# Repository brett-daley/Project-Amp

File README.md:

# Project-Amp
Small, portable headphone amplifier for the guitar. Complete with EQ and distortion.

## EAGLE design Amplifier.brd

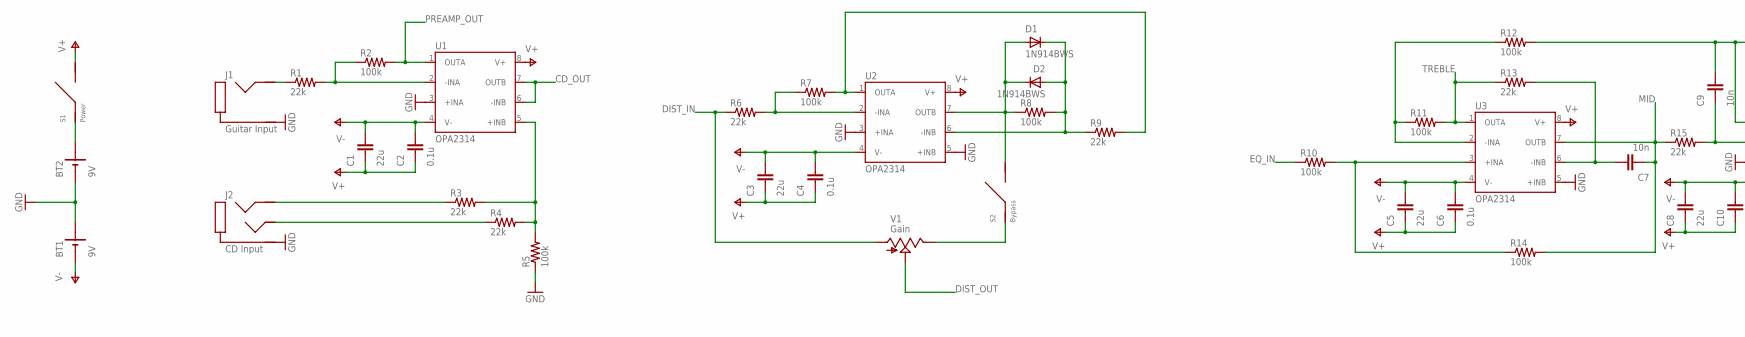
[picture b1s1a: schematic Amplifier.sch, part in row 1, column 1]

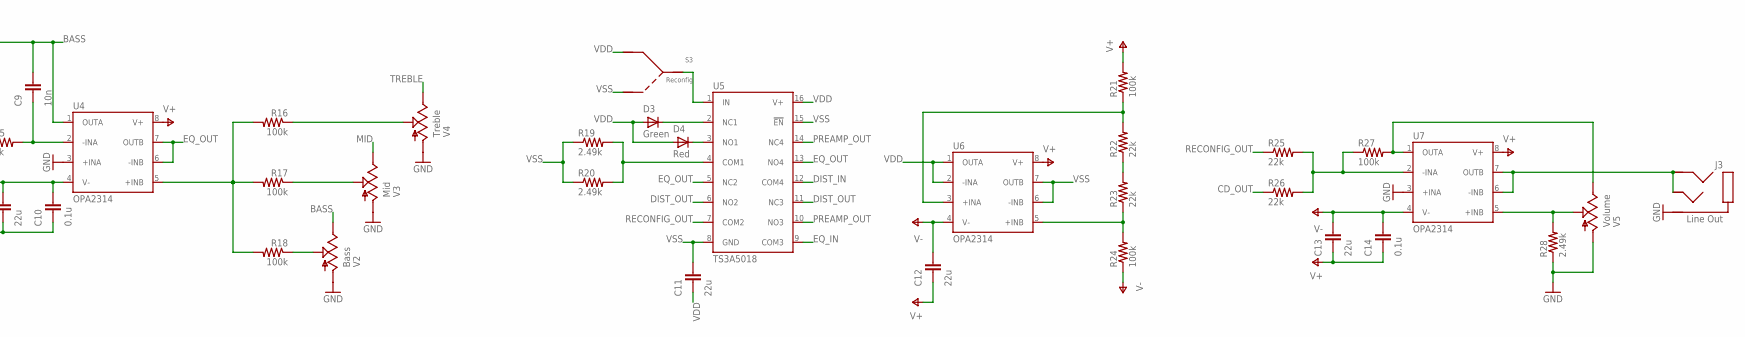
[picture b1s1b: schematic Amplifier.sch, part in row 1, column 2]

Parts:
BT1, BT2: 9V; 9V59X
C1, C3, C5, C8, C11, C12, C13: 22u; C1206
C2, C4, C6, C10, C14: 0.1u; C0402
C7, C9: 10n; ECW-F6103HL
D1, D2: 1N914BWS; SOD-323F
D3: Green; R0402
D4: Red; R0402
J1: Guitar Input; RA49C12B
J2: CD Input; SJ1-3513-SMT-TR
J3: Line Out; SJ1-3513-SMT-TR
R1, R3, R4, R6, R9, R13, R15, R22, R23, R25, R26: 22k; R0402
R2, R5, R7, R8, R10, R11, R12, R14, R16, R17, R18, R21, R24, R27: 100k; R0402
R19, R20, R28: 2.49k; R0402
S1: Power; TMS6T5B2M2RE
S2: Bypass; TMS6T5B2M2RE
S3: Reconfig; TMS1T5B2M2R
U1, U2, U3, U4, U6, U7: OPA2314; 8-SOIC
U5: TS3A5018; 16-SOIC
V1: Gain; P0915N-EC15BR10K
V2: Bass; P0915N-EC15BR10K
V3: Mid; P0915N-EC15BR10K
V4: Treble; P0915N-EC15BR10K
V5: Volume; P0915N-EC15BR10K

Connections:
BASS: C9.1, R12.2, U4.1 (OUTA), V2.3 (E)
CD_OUT: R26.1, U1.6 (-INB), U1.7 (OUTB)
DIST_IN: R6.1, U5.12 (COM4), V1.1 (A)
DIST_OUT: U5.6 (NO2), U5.11 (NC3), V1.2 (S)
EQ_IN: R10.1, U5.9 (COM3)
EQ_OUT: U4.6 (-INB), U4.7 (OUTB), U5.5 (NC2), U5.13 (NO4)
GND: BT1.4 (+), BT1.5 (+), BT1.6 (+), BT2.1 (-), BT2.2 (-), BT2.3 (-), J1.S1 (COM), J1.S2 (COM), J2.1 (COM), J3.1 (COM), R5.1, R28.1, U1.3 (+INA), U2.3 (+INA), U2.5 (+INB), U3.5 (+INB), U4.3 (+INA), U7.3 (+INA), V2.1 (A), V3.1 (A), V4.1 (A), V5.1 (A)
LINE_OUT: J3.2 (LEFT), J3.3 (RIGHT), U7.6 (-INB), U7.7 (OUTB)
MID: C7.2, R14.2, R15.1, U3.7 (OUTB), V3.3 (E)
unnamed: R21.1, R22.2, U6.3 (+INA)
unnamed: J1.T (SIG), R1.1
unnamed: R1.2, R2.1, U1.2 (-INA)
unnamed: R3.2, R4.2, R5.2, U1.5 (+INB)
unnamed: R22.1, R23.2
unnamed: J2.2 (LEFT), R4.1
unnamed: J2.3 (RIGHT), R3.1
unnamed: R23.1, R24.2, U6.5 (+INB)
unnamed: D3.2 (C), U5.2 (NC1)
unnamed: R19.2, R20.2, U5.4 (COM1)
unnamed: D1.2 (A), D2.1 (C), R8.1, S2.1, U2.7 (OUTB)
unnamed: D1.1 (C), D2.2 (A), R8.2, R9.1, U2.6 (-INB)
unnamed: R7.2, R9.2, U2.1 (OUTA)
unnamed: R6.2, R7.1, U2.2 (-INA)
unnamed: S2.3, V1.3 (E)
unnamed: R16.2, R17.2, R18.2, U4.5 (+INB)
unnamed: R16.1, V4.2 (S)
unnamed: R17.1, V3.2 (S)
unnamed: R18.1, V2.2 (S)
unnamed: R10.2, R14.1, U3.3 (+INA)
unnamed: R11.1, R12.1, U3.2 (-INA)
unnamed: C7.1, R13.2, U3.6 (-INB)
unnamed: C9.2, R15.2, U4.2 (-INA)
unnamed: R27.2, U7.1 (OUTA), V5.3 (E)
unnamed: R25.2, R26.2, R27.1, U7.2 (-INA)
unnamed: R28.2, U7.5 (+INB), V5.2 (S)
unnamed: BT2.4 (+), BT2.5 (+), BT2.6 (+), S1.3
unnamed: S3.2 (COM), U5.1 (IN)
unnamed: D4.2 (C), U5.3 (NO1)
PREAMP_OUT: R2.2, U1.1 (OUTA), U5.10 (NO3), U5.14 (NC4)
RECONFIG_OUT: R25.1, U5.7 (COM2)
TREBLE: R11.2, R13.1, U3.1 (OUTA), V4.3 (E)
V+: C1.2, C2.2, C3.2, C4.2, C5.2, C6.2, C8.2, C10.2, C12.2, C13.2, C14.2, R21.2, S1.1, U1.8 (V+), U2.8 (V+), U3.8 (V+), U4.8 (V+), U6.8 (V+), U7.8 (V+)
V-: BT1.1 (-), BT1.2 (-), BT1.3 (-), C1.1, C2.1, C3.1, C4.1, C5.1, C6.1, C8.1, C10.1, C12.1, C13.1, C14.1, R24.1, U1.4 (V-), U2.4 (V-), U3.4 (V-), U4.4 (V-), U6.4 (V-), U7.4 (V-)
VDD: C11.2, D3.1 (A), D4.1 (A), S3.3 (POS1), U5.16 (V+), U6.1 (OUTA), U6.2 (-INA)
VSS: C11.1, R19.1, R20.1, S3.1 (POS2), U5.8 (GND), U5.15 (!EN), U6.6 (-INB), U6.7 (OUTB)

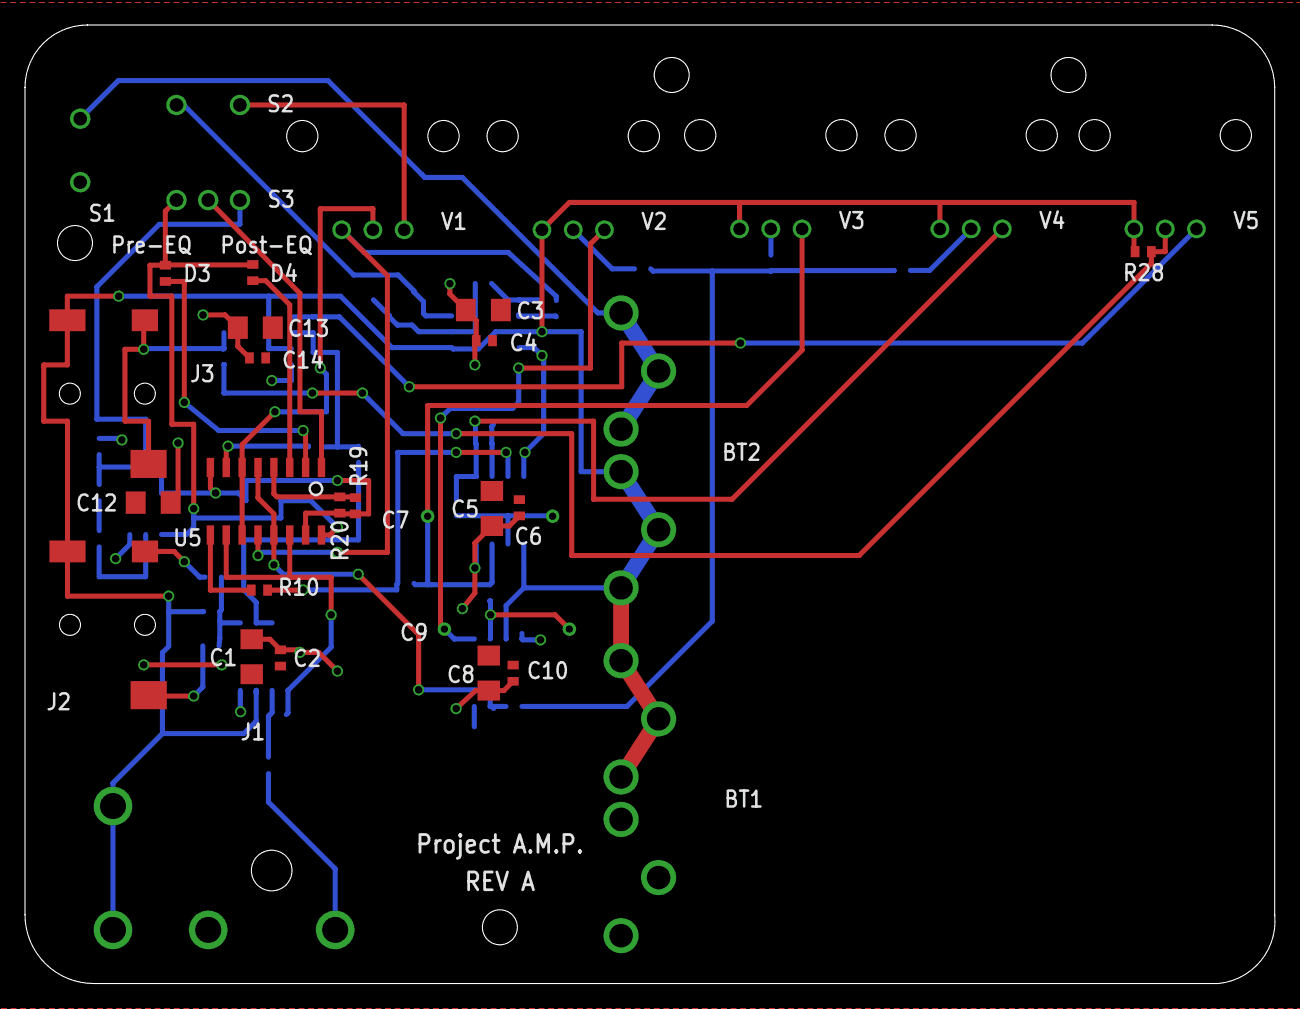
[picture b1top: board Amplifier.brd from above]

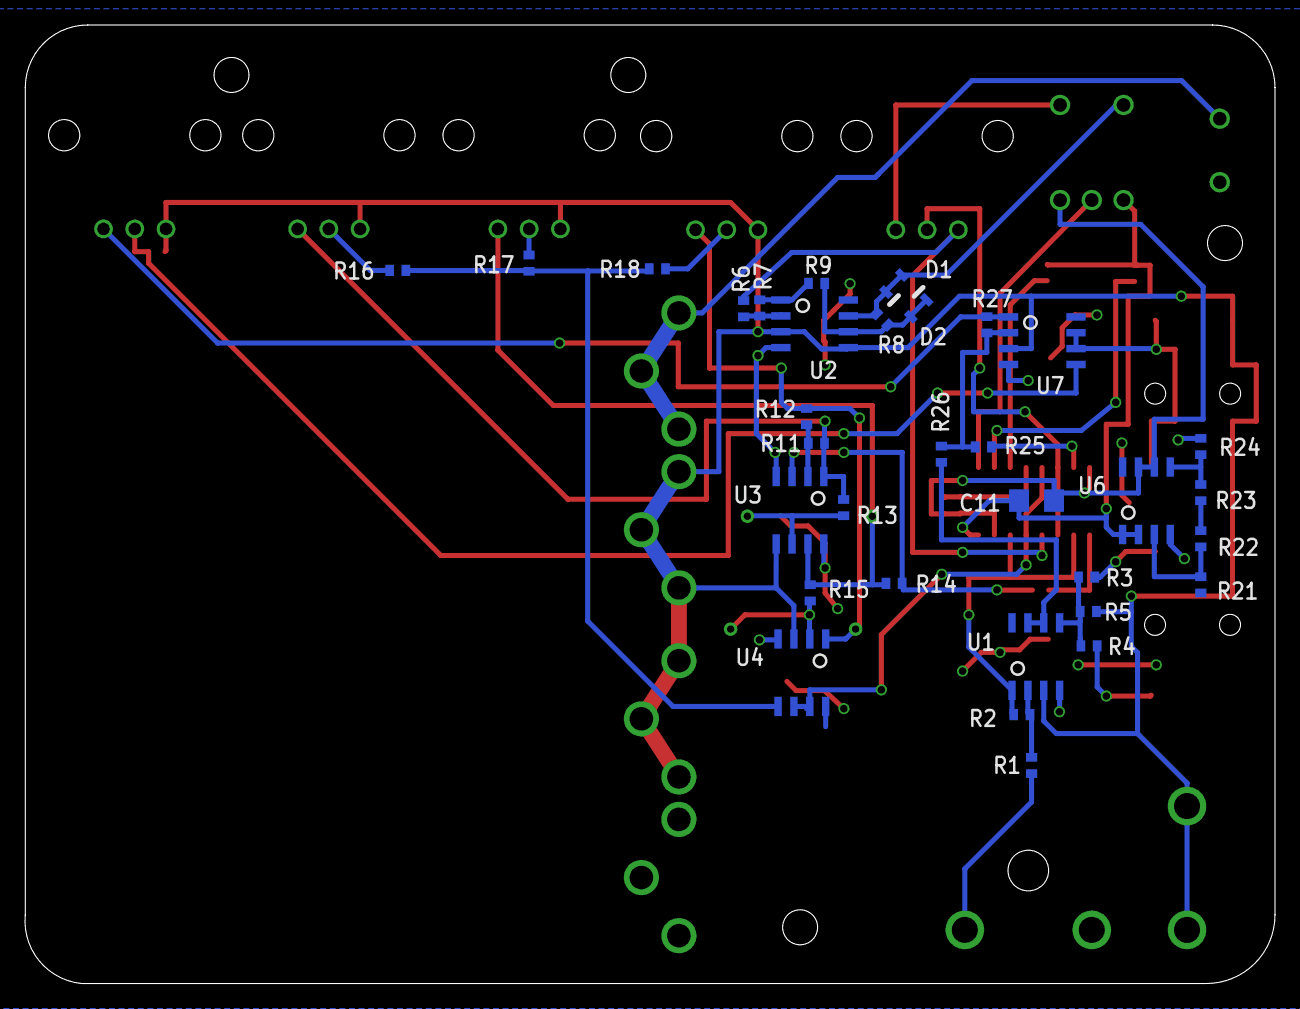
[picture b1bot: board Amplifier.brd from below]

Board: 2 copper layers, 100.0 x 76.7 mm, 66 parts (33 on the bottom side), 45 nets.

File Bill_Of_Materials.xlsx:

Item | Reference | Description | Manufacturer | Manufacturer PN | Digi-Key PN | Quantity
1 | BT1,BT2 | CONN BATT MALE/FEM 9V HORZ SNAP-ON | Keystone Electronics | 593/594 | 36-593-ND/36-594-ND | 2
2 | C1,C3,C5,C8,C11,C12,C13 | 22µF 25V Ceramic Capacitor X5R 1206 (3216 Metric) 0.126" L x 0.063" W (3.20mm x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 | Murata Electronics North America | GRM31CR61E226KE15L | 490-5527-2-ND | 7
3 | C2,C4,C6,C10,C14 | 0.10µF 25V Ceramic Capacitor X5R 0402 (1005 Metric) 0.039" L x 0.020" W (1.00mm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 | Murata Electronics North America | GRM155R61E104KA87D | 490-5920-1-ND | 5
4 | C7,C9 | 10000pF Film Capacitor 630V Polypropylene (PP), Metallized Radial 0.492" L x 0.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 | Panasonic Electronic Components | ECW-F6103HL | P12109-ND | 2
5 | D1,D2 | DIODE GEN PURP 75V 150MA SOD323F | Fairchild Semiconductor | 1N914BWS | 1N914BWSCT-ND | 2
6 | D3 | Green 569nm LED Indication Discrete 1.9V Clear Lens 0402 (1005 Metric) | Rohm Semiconductor | SML-P11MTT86 | 511-1652-1-ND | 1
7 | D4 | Red 621nm LED Indication Discrete 1.8V Clear Lens 0402 (1005 Metric) | Rohm Semiconductor | SML-P11UTT86 | 511-1653-1-ND | 1
8 | J1 | 6.35mm (0.250", 1/4") - Headphone Phone Jack Stereo Connector Solder | Switchcraft Inc. | RA49C12B | SC2083-ND | 1
9 | J2,J3 | 3.50mm (0.141", 1/8", Mini Plug) - Headphone Phone Jack Stereo Connector Solder | CUI Inc. | SJ1-3513-SMT-TR | CP1-3513SJCT-ND | 2
10 | R1,R3,R4,R6,R9,R13,R15,R22,R23,R25,R26 | RES SMD 22K OHM 1% 1/16W 0402 | Yageo | RC0402FR-0722KL | 311-22.0KLRCT-ND | 11
11 | R2,R5,R7,R8,R10,R11,R12,R14,R16,R17,R18,R21,R24,R27 | RES SMD 100K OHM 1% 1/16W 0402 | Yageo | RC0402FR-07100KL | 311-100KLRCT-ND | 14
12 | R19,R20,R28 | RES SMD 2.49K OHM 1% 1/16W 0402 | Yageo | RC0402FR-072K49L | 311-2.49KLRCT-ND | 3
13 | S1,S2 | Toggle Switch SPST Through Hole | TE Connectivity Alcoswitch Switches | TMS6T5B2M2RE | 450-2110-ND | 2
14 | S3 | Toggle Switch SPDT Through Hole | TE Connectivity Alcoswitch Switches | TMS1T5B2M2RE | 450-2103-ND | 1
15 | U1,U2,U3,U4,U6,U7 | IC OPAMP AUDIO 8MHZ 8SOIC | Texas Instruments | OPA2134UA | OPA2134UA-ND | 6
16 | U5 | IC SWITCH QUAD SPDT 16SOIC | Texas Instruments | TS3A5018DR | 296-17611-1-ND | 1
17 | V1,V2,V3,V4,V5 | POT 10K OHM 1/20W PLASTIC LINEAR | TT Electronics/BI | P0915N-EC15BR10K | 987-1666-ND | 5
 |  |  |  |  | Total: | 66

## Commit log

2016-06-19 Add files via upload
    Added custom Eagle library, schematics, board file, and Gerbers
2016-08-25 Restructure directories, upload images, include BOM
2016-08-25 Include EAGLE project files
2016-08-25 Fix error in page 2 of EAGLE schematics
2016-08-25 Reorganize schematics and EAGLE project files
2016-08-25 Add EAGLE library and LTSpice simulation
2016-10-17 Add revision to BOM
